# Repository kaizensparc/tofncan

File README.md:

# tofncan

## Directory Outline
- [`~/pcb/`](pcb) PCB project.
    - [`~/pcb/.kibot`](pcb/.kibot) KiBot configuration files.
    - [`~/pcb/3d_models`](pcb/3d_models) .STEP and .WRL model files for all project specific footprints.
    - [`~/pcb/datasheets`](pcb/datasheets) Data sheets for components used.
    - [`~/pcb/lib_fp.pretty`](pcb/lib_fp.pretty) Project specific footprint library.
    - [`~/pcb/kicad_project`](pcb/kicad_project) Kicad project. When starting a new KiCAD project in this directory, be sure to uncheck *Create a new directory for the project* in the **Create New Project** window.
    - [`~/pcb/lib_sch`](pcb/lib_sch) Project specific schematic symbol libraries.
        - [`~/pcb/lib_sch/lib.lib`](pcb/lib_sch/lib.lib) Project specific schematic symbol library.
    - [`~/pcb/page_layouts`](pcb/page_layouts) Page layouts for pdf outputs.
    - [`~/pcb/outputs`](pcb/outputs) Project output files generated by KiCad and/or KiBot (these are not kept under version control).
        - [`~/pcb/outputs/3d_models`](pcb/outputs/3d_models) Exported 3D models of the board.
        - [`~/pcb/outputs/assembly`](pcb/outputs/assembly) Exported assembly files.
        - [`~/pcb/outputs/bom`](pcb/outputs/bom) Exported BOM files.
        - [`~/pcb/outputs/fabrication`](pcb/outputs/fabrication) Exported production (gerber) files.
        - [`~/pcb/outputs/images`](pcb/outputs/images) Exported images and 3D board renders.
        - [`~/pcb/outputs/pdf`](pcb/outputs/pdf) Exported schematics, board layouts, dimension drawings.
- [`~/firmware/`](firmware) Firmware souce code and binaries.
- [`~/enclosure/`](enclosure) Mechanical CAD design files for the encloser or box. Create seperate directories for `.stl` or other files for 3d printing for easy accesss.

## Managing Schematic Libraries
Project specific symbols can be saved in [`~/pcb/lib_sch/lib.lib`](pcb/lib_sch/lib.lib). Link this library as a project specific library to the project **using a relative path** like `${KIPRJMOD}/../lib_sch/lib.lib`.

### Saving a copy of the global symbols.
The global symbols are pulled from Github when the repository is cloned, and this can cause problems if the global symbols have changed in the meantime. To prevent this, KiCad automatically creates a backup in the project folder of the symbols currently in use named `<<PROJECT NAME>>-cache.lib`. 

To make sure everyone uses the same, you can convert the backup of the symbol library to a symbol library. To do this you need to move this file to  [`~/pcb/lib_sch`](pcb/lib_sch) and rename it to `<<PROJECT NAME>>.lib`. After this, you can add this symbol library as a project-specific symbol library and replace all symbols with the symbols from this library. **NOTE: Do this only after you've completed your whole schematic design!**

## Managing Footprints
Project specific footprints can be saved in [`~/pcb/lib_fp/lib_fp.pretty`](pcb/lib_fp/lib_fp.pretty). Link this library as a project specific library to the project **using a relative path** like `${KIPRJMOD}/../lib_fp/lib_fp.pretty`. Global symbols that are used can be copied to this folder and replaced with this local variant. 

## Managing 3D models of components
3D models for project specific components should be saved in [`~/pcb/3d_models`](pcb/3d_models). Then they can be linked to the matching footprint **using a relative path** like `${KIPRJMOD}/../3d_models/filename.step`.

## Managing the BOM information
Add the following field name templates in Eeschema (`preferences >> Preferences... >> Field Name Templates`):

| Name     | Visible            | URL                  | _Description_                                                                                     |
|:-------- | :----------------: | :------------------: | :------------------------------------------------------------------------------------------------ |
| `MFN`    | :white_check_mark: | :white_large_square: | _Manufacturer name._                                                                              |
| `MFP`    | :white_check_mark: | :white_large_square: | _Manufacturer product number._                                                                    |
| `LCSC#`  | :white_check_mark: | :white_large_square: | _LCSC/JLCPCB part number (leave part number empty if not using JLCPCB assembly)._                 |
| `Config` | :white_check_mark: | :white_large_square: | _Board configuration to apply this part to or `DNF` if part should not be fitted on final board._ |

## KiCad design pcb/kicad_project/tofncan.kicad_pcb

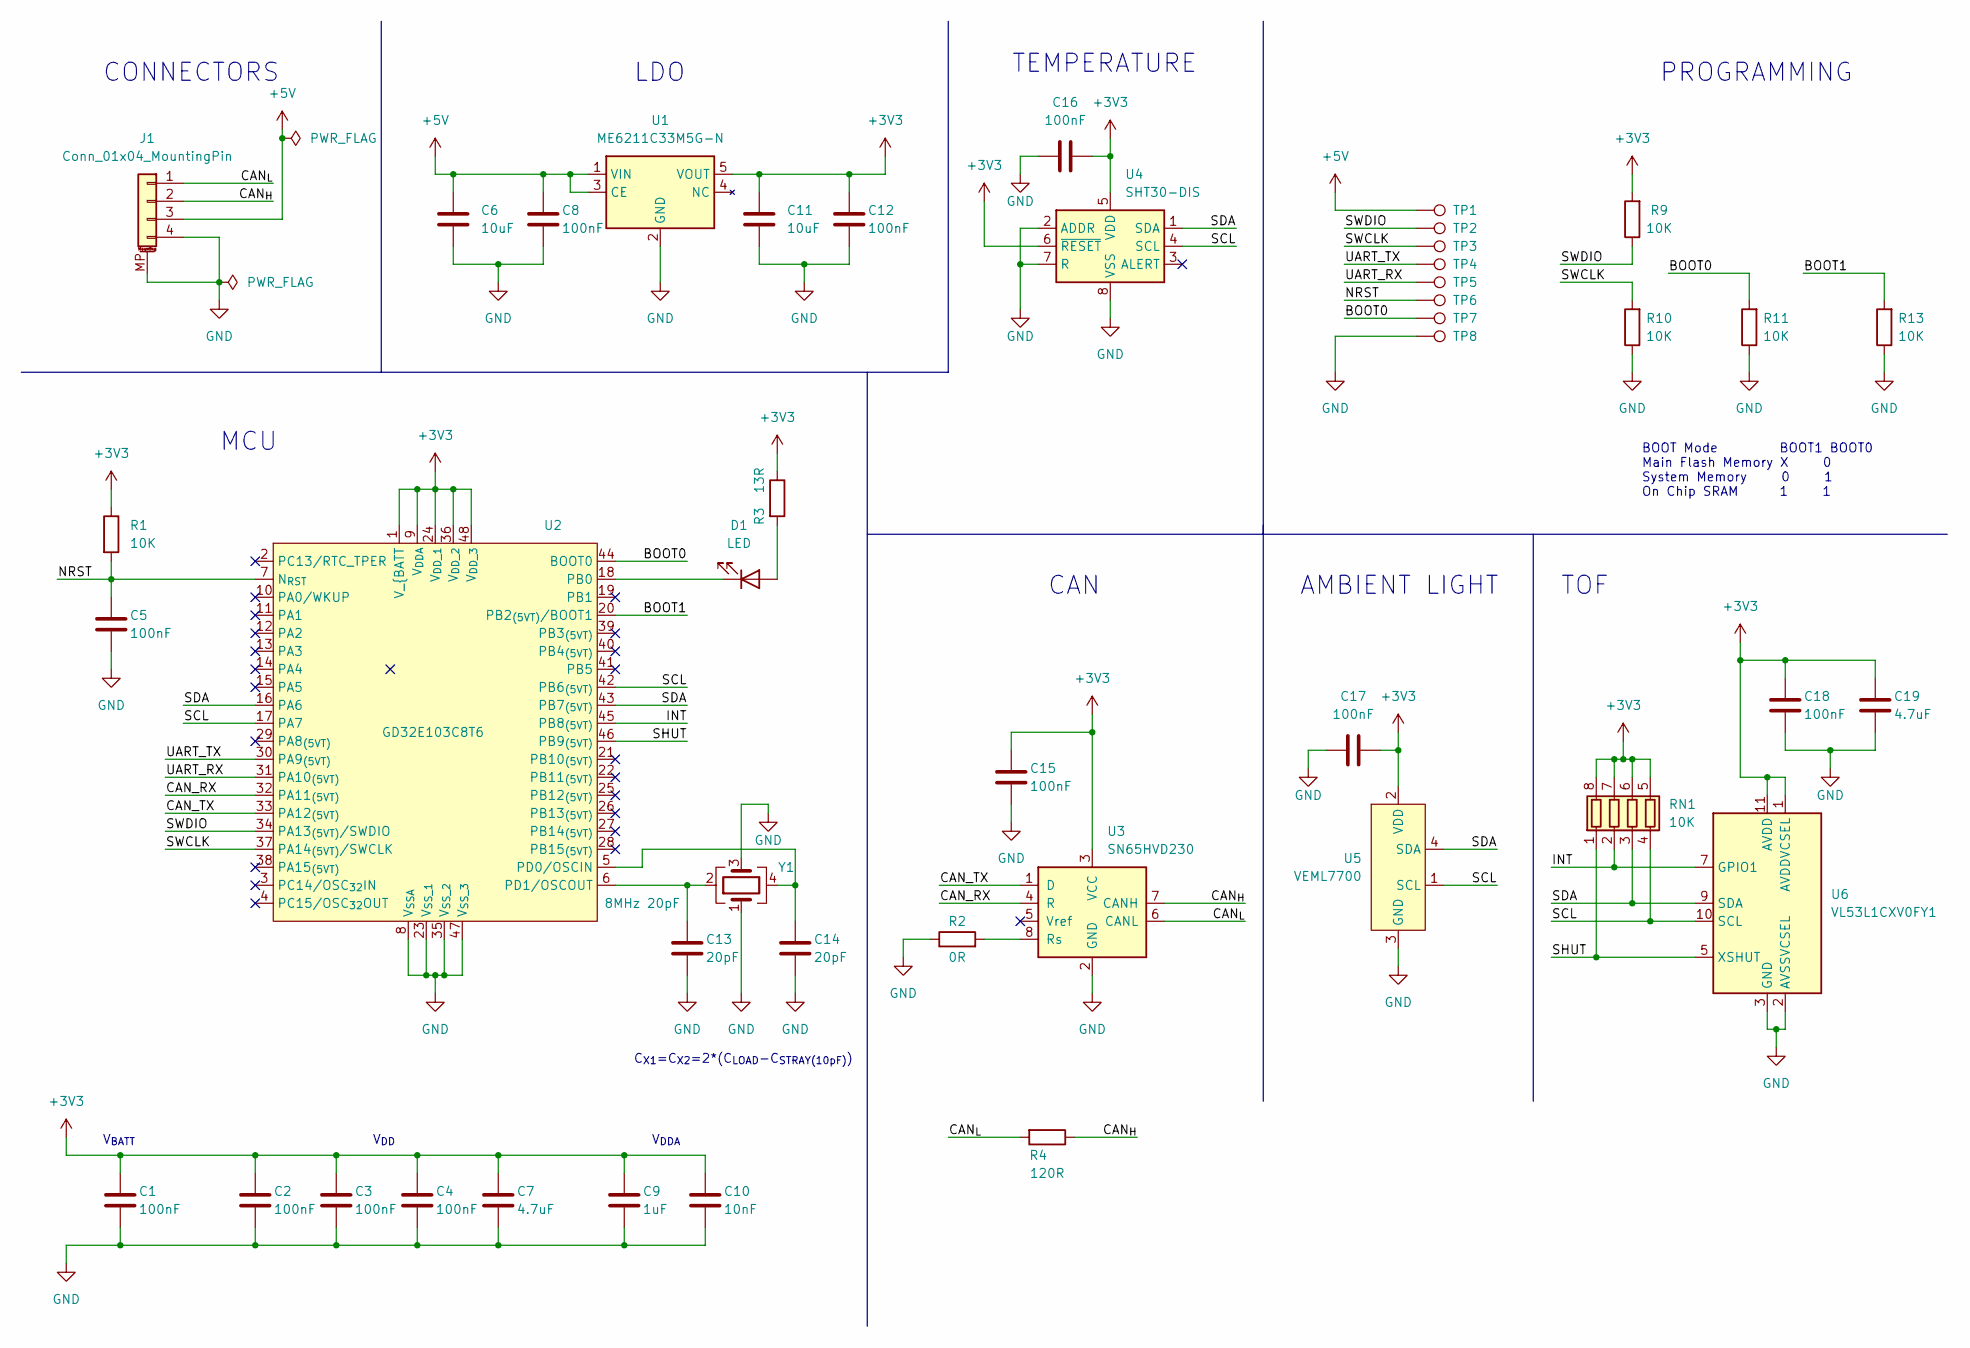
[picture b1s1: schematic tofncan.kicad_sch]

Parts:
C1, C2, C3, C4, C5, C8, C12, C15, C16, C17, C18: 100nF; C_0402_1005Metric; LCSC C1525
C6, C11: 10uF; C_0805_2012Metric; LCSC C88484
C7, C19: 4.7uF; C_0402_1005Metric; LCSC C23733
C9: 1uF; C_0402_1005Metric; LCSC C52923
C10: 10nF; C_0402_1005Metric; LCSC C400948
C13, C14: 20pF; C_0402_1005Metric; LCSC C76959
D1: LED; LED_0603_1608Metric; LCSC C965809
J1: Conn_01x04_MountingPin; JST_SH_BM04B-SRSS-TB_1x04-1MP_P1.00mm_Vertical; LCSC C160390
R1, R9, R10, R11, R13: 10K; R_0402_1005Metric; LCSC C60490
R2: 0R; R_0402_1005Metric; LCSC C106231
R3: 13R; R_0402_1005Metric; LCSC C412909
R4: 120R; R_0402_1005Metric; LCSC C114758
RN1: 10K; R_Array_Convex_4x0402; LCSC C326872
TP1, TP2, TP3, TP4, TP5, TP6, TP7, TP8: TestPoint; TestPoint_Pad_D1.0mm
U1: ME6211C33M5G-N; SOT-23-5; LCSC C82942
U2: GD32E103C8T6; LQFP-48_7x7mm_P0.5mm; LCSC C350804
U3: SN65HVD230; SOIC-8_3.9x4.9mm_P1.27mm; LCSC C12084
U4: SHT30-DIS; Sensirion_DFN-8-1EP_2.5x2.5mm_P0.5mm_EP1.1x1.7mm; LCSC C77361
U5: VEML7700; VEML7700-TOP; LCSC C504893
U6: VL53L1CXV0FY1; ST_VL53L1X; LCSC C190004
Y1: 8MHz 20pF; Crystal_SMD_3225-4Pin_3.2x2.5mm; LCSC C720915

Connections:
+3V3: C1.1, C2.1, C3.1, C4.1, C7.1, C9.1, C10.1, C11.1, C12.1, C15.1, C16.2, C17.2, C18.1, C19.1, R1.1, R3.1, R9.2, RN1.5 (R4.2), RN1.6 (R3.2), RN1.7 (R2.2), RN1.8 (R1.2), U1.5 (VOUT), U2.1 (V_{BATT), U2.9 (V_{DDA}), U2.24 (V_{DD_1}), U2.36 (V_{DD_2}), U2.48 (V_{DD_3}), U3.3 (VCC), U4.5 (VDD), U4.6 (~RESET), U5.2 (VDD), U6.1 (AVDDVCSEL), U6.11 (AVDD)
+5V: C6.1, C8.1, J1.3, TP1.1, U1.1 (VIN), U1.3 (CE)
/BOOT0: R11.2, TP7.1, U2.44 (BOOT0)
/BOOT1: R13.2, U2.20 (PB2_{(5VT)}/BOOT1)
/CAN_RX: U2.32 (PA11_{(5VT)}), U3.4 (R)
/CAN_TX: U2.33 (PA12_{(5VT)}), U3.1 (D)
/CAN_{H}: J1.2, R4.1, U3.7 (CANH)
/CAN_{L}: J1.1, R4.2, U3.6 (CANL)
/INT: RN1.2 (R2.1), U2.45 (PB8_{(5VT)}), U6.7 (GPIO1)
/NRST: C5.1, R1.2, TP6.1, U2.7 (N_{RST})
/SCL: RN1.4 (R4.1), U2.17 (PA7), U2.42 (PB6_{(5VT)}), U4.4 (SCL), U5.1 (SCL), U6.10 (SCL)
/SDA: RN1.3 (R3.1), U2.16 (PA6), U2.43 (PB7_{(5VT)}), U4.1 (SDA), U5.4 (SDA), U6.9 (SDA)
/SHUT: RN1.1 (R1.1), U2.46 (PB9_{(5VT)}), U6.5 (XSHUT)
/SWCLK: R10.2, TP3.1, U2.37 (PA14_{(5VT)}/SWCLK)
/SWDIO: R9.1, TP2.1, U2.34 (PA13_{(5VT)}/SWDIO)
/UART_RX: TP5.1, U2.31 (PA10_{(5VT)})
/UART_TX: TP4.1, U2.30 (PA9_{(5VT)})
GND: C1.2, C2.2, C3.2, C4.2, C5.2, C6.2, C7.2, C8.2, C9.2, C10.2, C11.2, C12.2, C13.2, C14.2, C15.2, C16.1, C17.1, C18.2, C19.2, J1.4, J1.MP (MountPin), R2.1, R10.1, R11.1, R13.1, TP8.1, U1.2 (GND), U2.8 (V_{SSA}), U2.23 (V_{SS_1}), U2.35 (V_{SS_2}), U2.47 (V_{SS_3}), U3.2 (GND), U4.2 (ADDR), U4.7 (R), U4.8 (VSS), U4.9 (VSS), U5.3 (GND), U6.2 (AVSSVCSEL), U6.3 (GND), U6.4 (GND), U6.6 (GND), U6.12 (GND), Y1.1, Y1.3
unnamed: C13.1, U2.6 (PD1/OSCOUT), Y1.2
unnamed: C14.1, U2.5 (PD0/OSCIN), Y1.4
unnamed: D1.1 (K), U2.18 (PB0)
unnamed: D1.2 (A), R3.2
unnamed: R2.2, U3.8 (Rs)

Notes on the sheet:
BOOT Mode BOOT1 BOOT0 Main Flash Memory X 0 System Memory 0 1 On Chip SRAM 1 1
C_{X1}=C_{X2}=2*(C_{LOAD}-C_{STRAY(10pF)})
CONNECTORS
TOF
V_{DD}
V_{DDA}
PROGRAMMING
AMBIENT LIGHT
MCU
TEMPERATURE
V_{BATT}
LDO
CAN

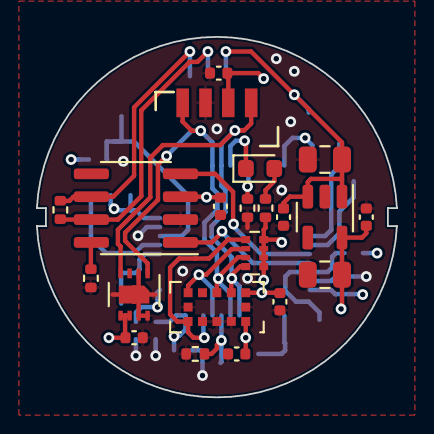
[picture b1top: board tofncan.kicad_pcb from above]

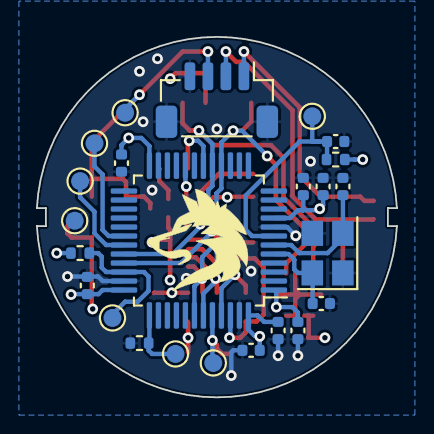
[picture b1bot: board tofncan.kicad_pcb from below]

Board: 4 copper layers, 20.0 x 20.0 mm, 45 parts (24 on the bottom side), 23 nets.

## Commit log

2022-11-08 Add kicad skeleton
2022-11-08 Add gitignore and github workflows
2022-11-15 Add first version of PCB
2023-01-05 Add example firmware
2023-05-10 Add CAN bus layer
2023-05-11 Add configuration registers
2023-10-09 UUse upstreamed repos for PAC/HAL
2023-10-09 Update chip description with new syntax
